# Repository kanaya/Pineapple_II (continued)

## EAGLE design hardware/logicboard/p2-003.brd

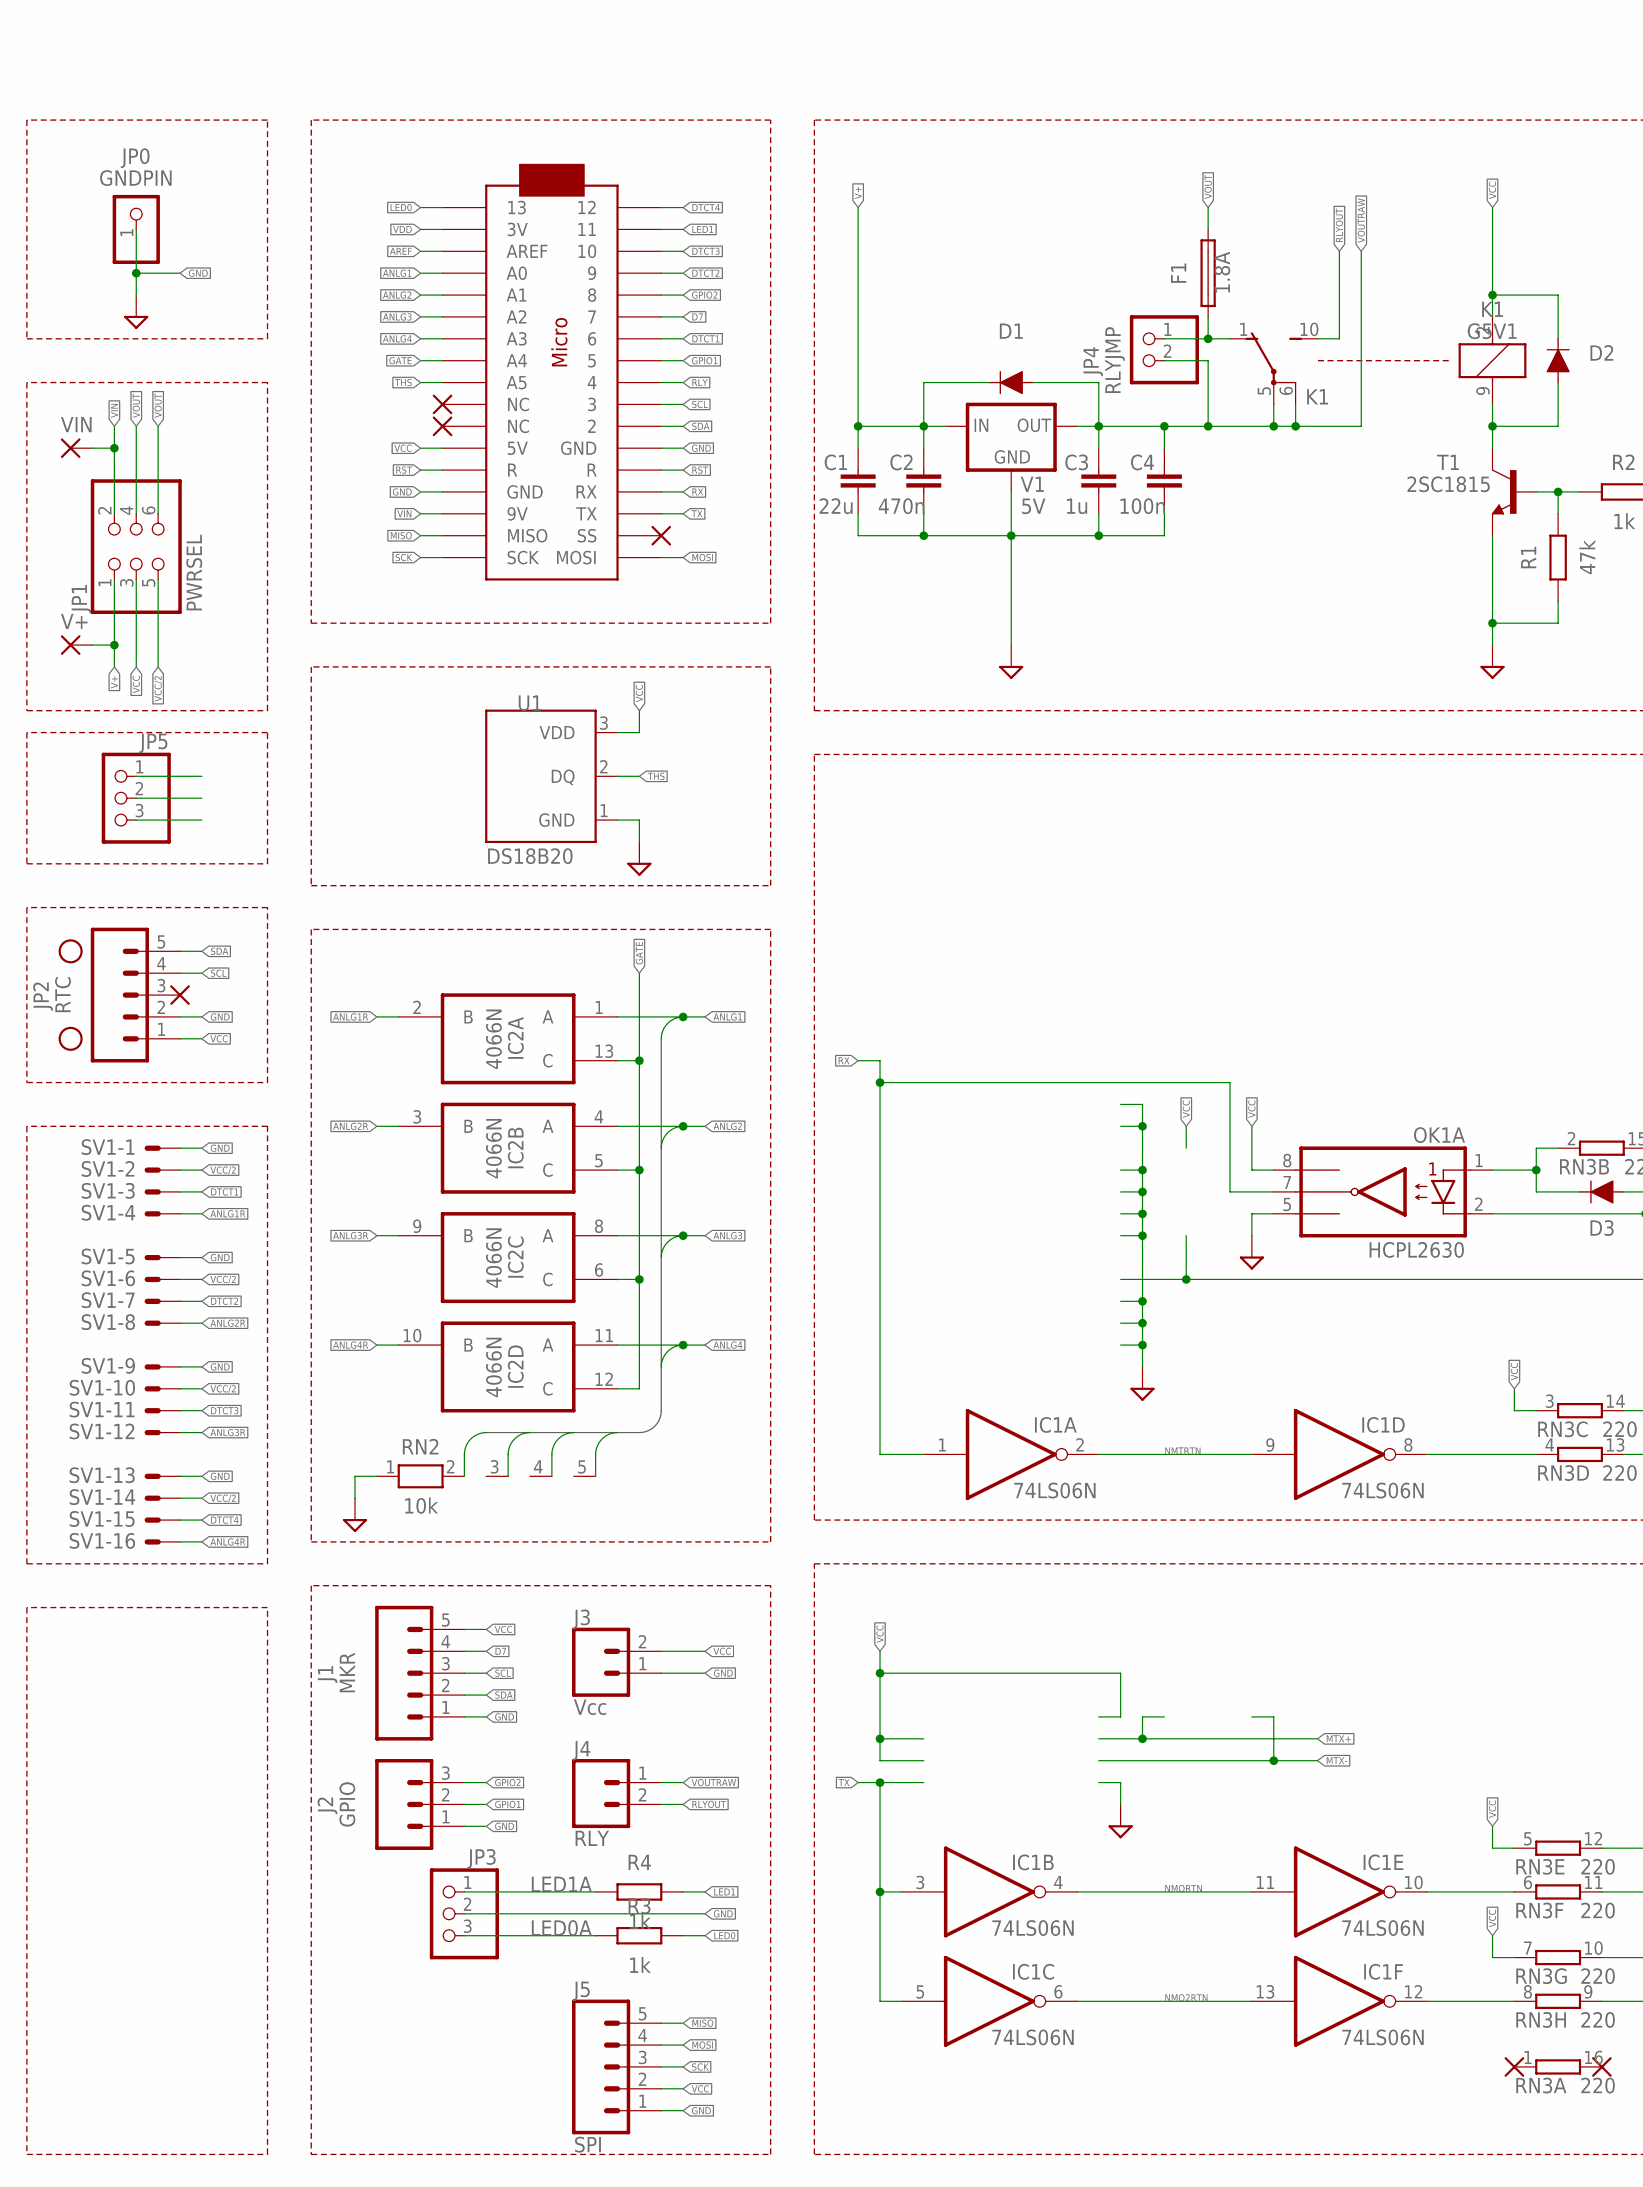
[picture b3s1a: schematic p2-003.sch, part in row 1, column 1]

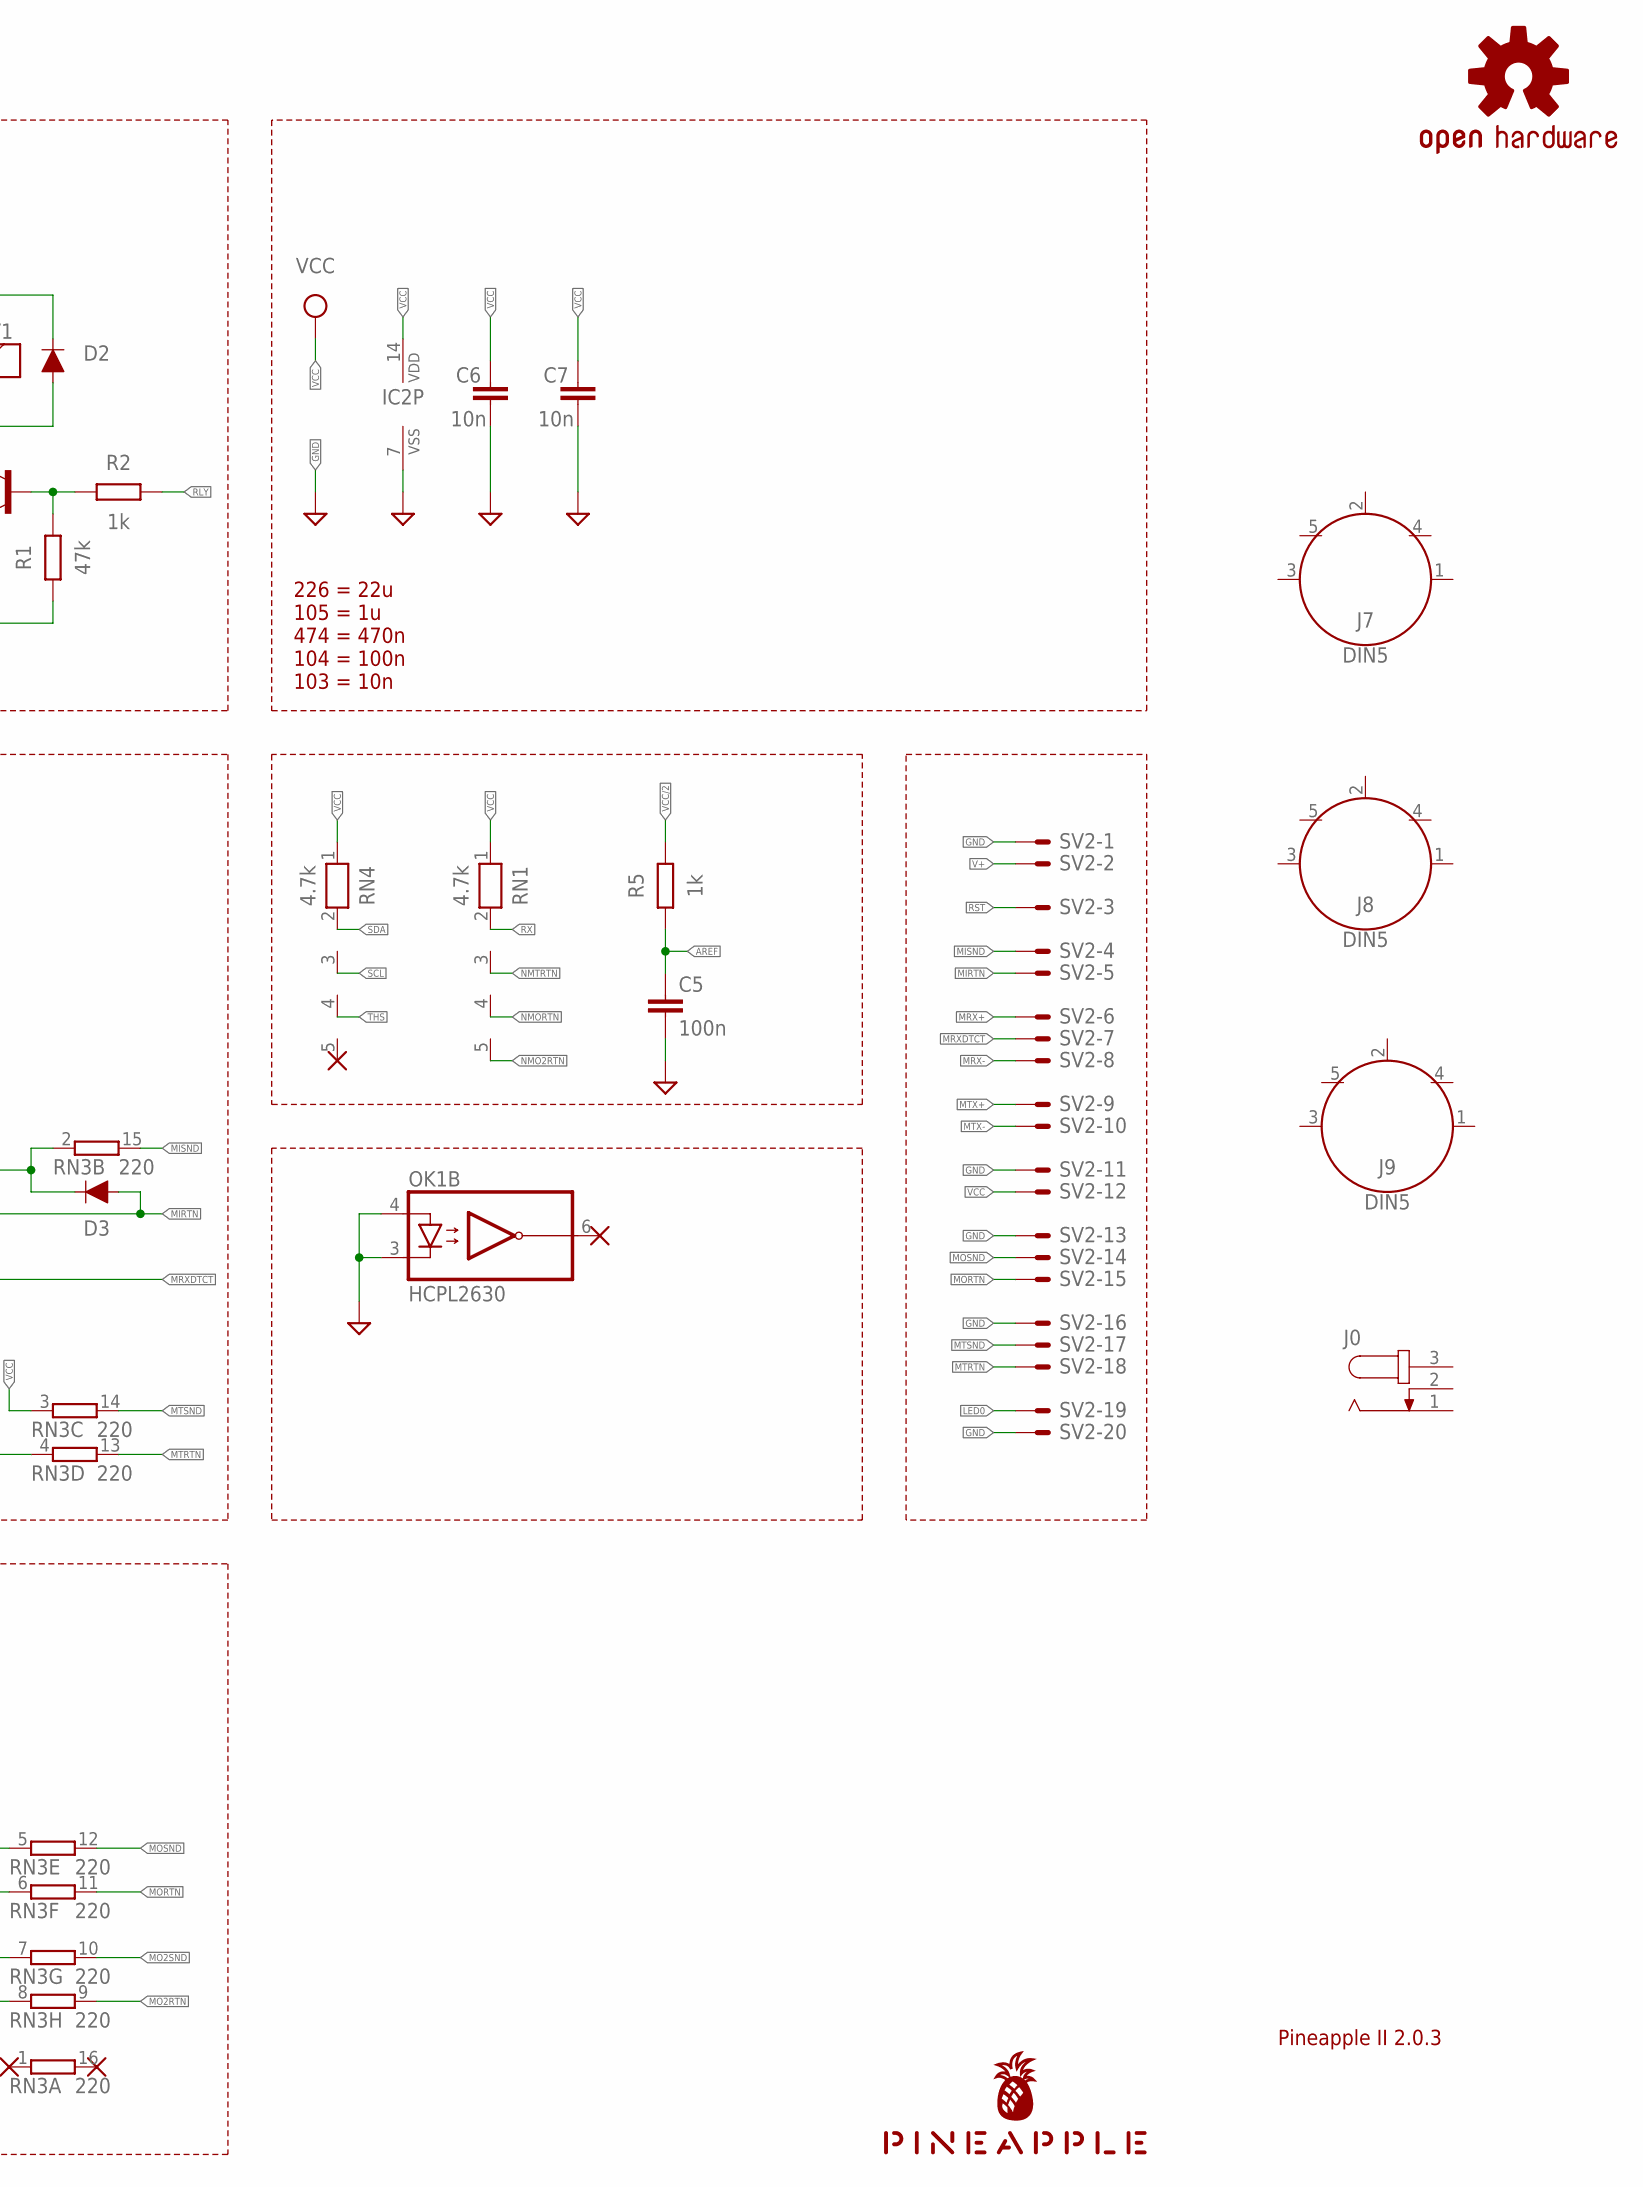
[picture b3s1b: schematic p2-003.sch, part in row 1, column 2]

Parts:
C1: 22u; C025-050X050
C2: 470n; C050-024X044
C3: 1u; C050-024X044
C4, C5: 100n; C025-024X044
C6, C7: 10n; C025-024X044
D1, D2, D3: DIODE-1N4148
F1: 1.8A; TE5
H1, H2: STAND-OFF
IC1: 74LS06N; DIL14
IC2: 4066N; DIL14
J0: JACK-PLUG0; SPC4077
J1: MKR; JST-5-PTH
J2: GPIO; JST-3-PTH
J3: Vcc; JST-2-PTH
J4: RLY; JST-2-SMD
J5: SPI; JST-5-PTH-VERT
J7, J8, J9: DIN5; DIN5-RA-PTH
JP0: GNDPIN; 1X01
JP1: PWRSEL; 2X03
JP2: RTC; 1X05
JP3, JP5: PINHD-1X3; 1X03
JP4: RLYJMP; 1X02
K1: G5V1
LOGO1: OSHW-LOGOS-COPPER; OSHW-LOGO-S_COPPER
MC1: ARDUINOMICRO
OK1: HCPL2630; DIL08
R1: 47k; 0204/5
R2, R3, R4, R5: 1k; 0204/5
RN1, RN4: 4.7k; RN-5
RN2: 10k; RN-5
RN3: 220; DIL16
SV1: ML16LE; ML16L
SV2: ML20LE; ML20L
T1: 2SC1815; TO92-ECB
U1: DS18B20; TO-92-AMMO
U$1: PINEAPPLE450_SILK
V1: 5V; 78XXL
V+: SMD2; SMD1,27-2,54
VIN: SMD2; SMD1,27-2,54

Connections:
ANLG1: IC2.1 (A), MC1.P$31 (A0), RN2.2
ANLG1R: IC2.2 (B), SV1.4
ANLG2: IC2.4 (A), MC1.P$30 (A1), RN2.3
ANLG2R: IC2.3 (B), SV1.8
ANLG3: IC2.8 (A), MC1.P$29 (A2), RN2.4
ANLG3R: IC2.9 (B), SV1.12
ANLG4: IC2.11 (A), MC1.P$28 (A3), RN2.5
ANLG4R: IC2.10 (B), SV1.16
AREF: C5.1, MC1.P$32 (AREF), R5.1
D7: J1.4, MC1.P$6 (7)
DTCT1: MC1.P$7 (6), SV1.3
DTCT2: MC1.P$4 (9), SV1.7
DTCT3: MC1.P$3 (10), SV1.11
DTCT4: MC1.P$1 (12), SV1.15
GATE: IC2.5 (C), IC2.6 (C), IC2.12 (C), IC2.13 (C), MC1.P$27 (A4)
GND: C1.2, C2.2, C3.2, C4.2, C5.2, C6.2, C7.2, IC1.7 (GND), IC2.7 (VSS), J1.1, J2.1, J3.1, J5.1, JP0.1, JP2.2, JP3.2, JP5.1, MC1.P$12 (GND), MC1.P$21 (GND), OK1.3 (C2), OK1.4 (A2), OK1.5 (GND), R1.1, RN2.1, SV1.1, SV1.5, SV1.9, SV1.13, SV2.1, SV2.11, SV2.13, SV2.16, SV2.20, T1.E, U1.1 (GND), V1.GND
GPIO1: J2.2, MC1.P$8 (5)
GPIO2: J2.3, MC1.P$5 (8)
LED0: MC1.P$34 (13), R3.2, SV2.19
LED0A: JP3.3, R3.1
LED1: MC1.P$2 (11), R4.2
LED1A: JP3.1, R4.1
MIDIINSND: D3.C, OK1.1 (A1), RN3.2 (1)
MIRTN: D3.A, OK1.2 (C1), SV2.5
MISND: RN3.15 (2), SV2.4
MISO: J5.5, MC1.P$19 (MISO)
MO2RTN: RN3.9 (2)
MO2RTNRAW: IC1.12 (O), RN3.8 (1)
MO2SND: RN3.10 (2)
MORTN: RN3.11 (2), SV2.15
MORTNRAW: IC1.10 (O), RN3.6 (1)
MOSI: J5.4, MC1.P$17 (MOSI)
MOSND: RN3.12 (2), SV2.14
MRX+: SV2.6
MRX-: SV2.8
MRXDTCT: SV2.7
MTRTN: RN3.13 (2), SV2.18
MTRTNRAW: IC1.8 (O), RN3.4 (1)
MTSND: RN3.14 (2), SV2.17
MTX+: SV2.9
MTX-: SV2.10
NMO2RTN: IC1.6 (O), IC1.13 (I), RN1.5
NMORTN: IC1.4 (O), IC1.11 (I), RN1.4
NMTRTN: IC1.2 (O), IC1.9 (I), RN1.3
RLY: MC1.P$9 (4), R2.2
RLYDRV: R1.2, R2.1, T1.B
RLYOUT: J4.2 (1), K1.10 (S)
RLYSNK: D2.A, K1.9 (2), T1.C
RST: MC1.P$13 (R), MC1.P$22 (R), SV2.3
RX: IC1.1 (I), MC1.P$14 (RX), OK1.7 (VO1), RN1.2
SCK: J5.3, MC1.P$18 (SCK)
SCL: J1.3, JP2.4, MC1.P$10 (3), RN4.3
SDA: J1.2, JP2.5, MC1.P$11 (2), RN4.2
THS: MC1.P$26 (A5), RN4.4, U1.2 (DQ)
TX: IC1.3 (I), IC1.5 (I), MC1.P$15 (TX)
V+: C1.1, C2.1, D1.C, JP1.1, JP5.3, SV2.2, V1.IN, V+.1
VCC: C6.1, C7.1, D2.C, IC1.14 (VCC), IC2.14 (VDD), J1.5, J3.2, J5.2, JP1.3, JP2.1, JP5.2, K1.2 (1), MC1.P$23 (5V), OK1.8 (VCC), RN1.1, RN3.3 (1), RN3.5 (1), RN3.7 (1), RN4.1, SV2.12, U1.3 (VDD)
VCC/2: JP1.5, R5.2, SV1.2, SV1.6, SV1.10, SV1.14
VDD: MC1.P$33 (3V)
VIN: JP1.2, MC1.P$20 (9V), VIN.1
VOUT: F1.2, JP1.4, JP1.6
VOUTRAW: C3.1, C4.1, D1.A, J4.1 (2), JP4.2, K1.5, K1.6, V1.OUT
VOUTRAW2: F1.1, JP4.1, K1.1 (O)

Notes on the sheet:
Pineapple II 2.0.3
226 = 22u 105 = 1u 474 = 470n 104 = 100n 103 = 10n

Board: 2 copper layers, 51 parts (1 on the bottom side), 55 nets, no tracks yet.

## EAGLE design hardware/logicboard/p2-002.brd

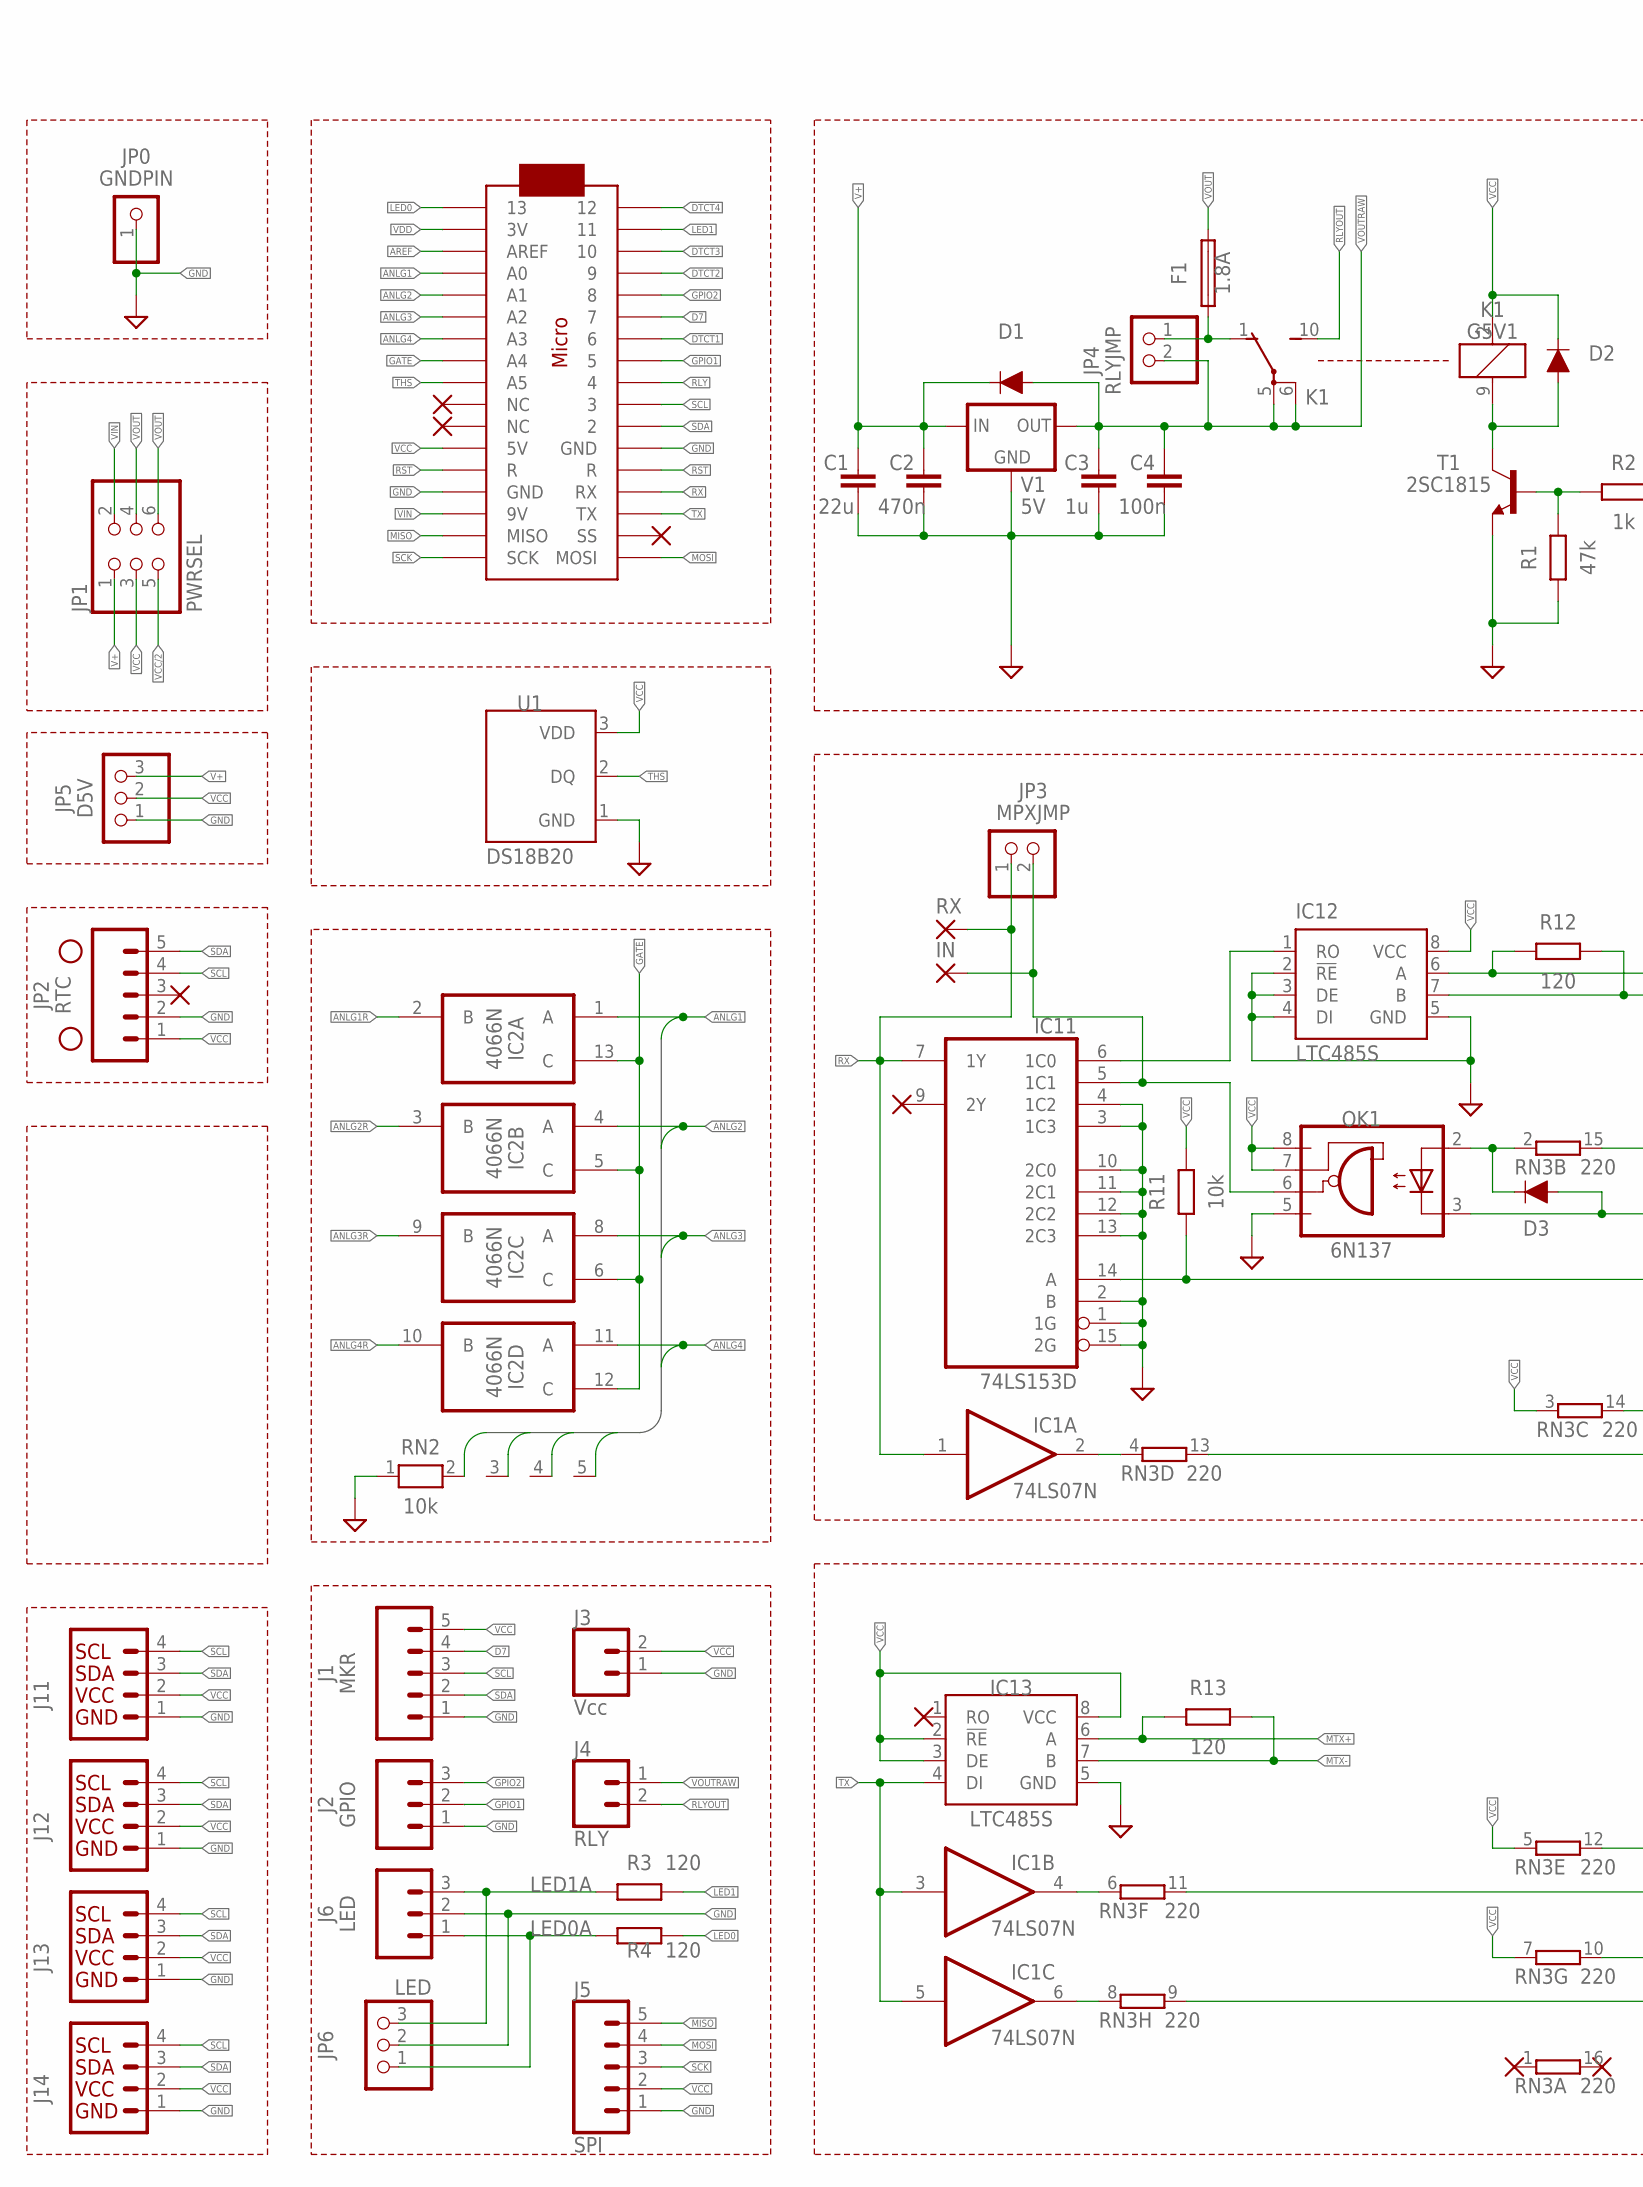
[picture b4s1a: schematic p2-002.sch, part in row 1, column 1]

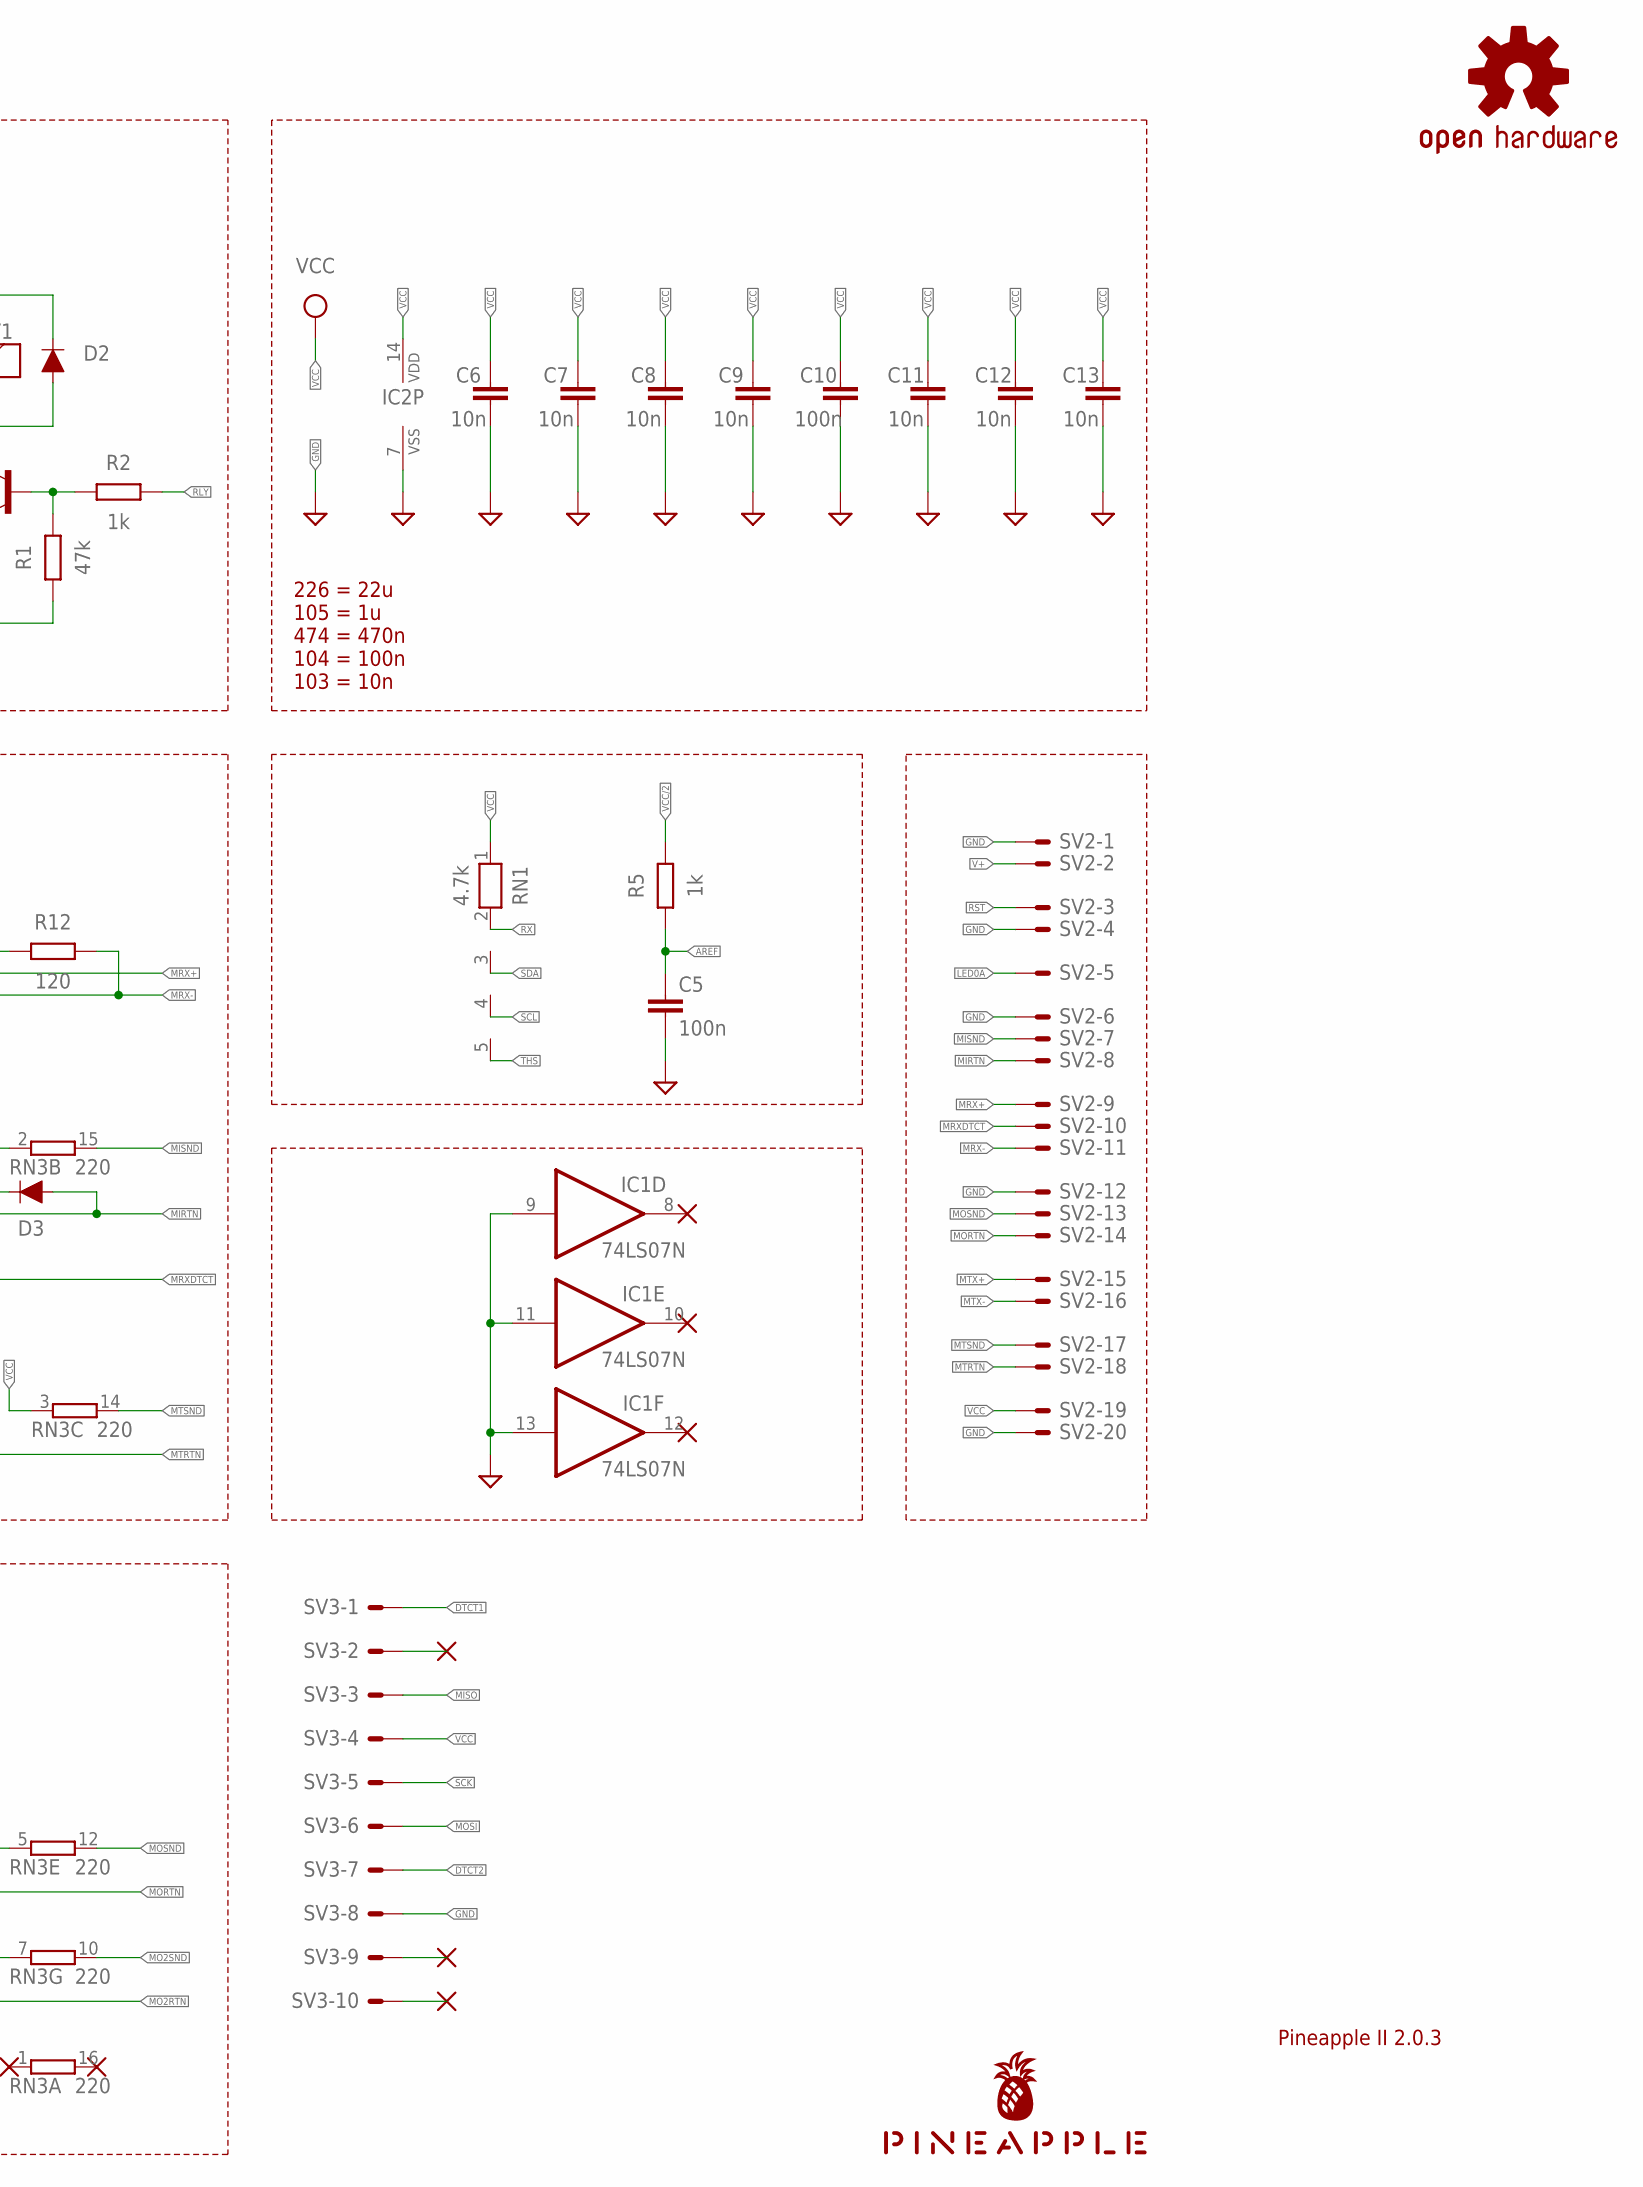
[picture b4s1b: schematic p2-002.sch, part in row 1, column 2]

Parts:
C1: 22u; C025-050X050
C2: 470n; C050-024X044
C3: 1u; C050-024X044
C4, C5, C10: 100n; C025-024X044
C6, C7, C8, C9: 10n; C025-024X044
C11, C12, C13: 10n; C2012
D1, D2, D3: DIODE-1N4148
F1: 1.8A; TE5
H1, H2: STAND-OFF
IC1: 74LS07N; DIL14
IC2: 4066N; DIL14
IC11: 74LS153D; SO16
IC12, IC13: LTC485S; SOIC8
IN: SMD2; SMD1,27-2,54
J1: MKR; JST-5-PTH
J2: GPIO; JST-3-PTH
J3: Vcc; JST-2-PTH
J4: RLY; JST-2-SMD
J5: SPI; JST-5-PTH-VERT
J6: LED; JST-3-PTH
J11, J12, J13, J14: Qwiic; 1X04_1MM_RA
JP0: GNDPIN; 1X01
JP1: PWRSEL; 2X03
JP2: RTC; 1X05
JP3: MPXJMP; 1X02
JP4: RLYJMP; 1X02
JP5: D5V; 1X03
JP6: LED; 1X03
K1: G5V1
LOGO1: OSHW-LOGOS-COPPER; OSHW-LOGO-S_COPPER
MC1: ARDUINOMICRO
OK1: 6N137; DIL08
R1: 47k; 0204/5
R2, R5: 1k; 0204/5
R3, R4: 120; 0204/5
R11: 10k; M2012
R12, R13: 120; M2012
RN1: 4.7k; RN-5
RN2: 10k; RN-5
RN3: 220; DIL16
RX: SMD2; SMD1,27-2,54
SV2: ML20LE; ML20L
SV3: ML10LE; ML10L
T1: 2SC1815; TO92-ECB
U1: DS18B20; TO-92-AMMO
U$1: PINEAPPLE450_SILK
V1: 5V; 78XXL

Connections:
ANLG1: IC2.1 (A), MC1.P$31 (A0), RN2.2
ANLG1R: IC2.2 (B)
ANLG2: IC2.4 (A), MC1.P$30 (A1), RN2.3
ANLG2R: IC2.3 (B)
ANLG3: IC2.8 (A), MC1.P$29 (A2), RN2.4
ANLG3R: IC2.9 (B)
ANLG4: IC2.11 (A), MC1.P$28 (A3), RN2.5
ANLG4R: IC2.10 (B)
AREF: C5.1, MC1.P$32 (AREF), R5.1
D7: J1.4, MC1.P$6 (7)
DTCT1: MC1.P$7 (6), SV3.1
DTCT2: MC1.P$4 (9), SV3.7
DTCT3: MC1.P$3 (10)
DTCT4: MC1.P$1 (12)
GATE: IC2.5 (C), IC2.6 (C), IC2.12 (C), IC2.13 (C), MC1.P$27 (A4)
GND: C1.2, C2.2, C3.2, C4.2, C5.2, C6.2, C7.2, C8.2, C9.2, C10.2, C11.2, C12.2, C13.2, IC1.7 (GND), IC1.9 (I), IC1.11 (I), IC1.13 (I), IC2.7 (VSS), IC11.1 (1G), IC11.2 (B), IC11.3 (1C3), IC11.4 (1C2), IC11.8 (GND), IC11.10 (2C0), IC11.11 (2C1), IC11.12 (2C2), IC11.13 (2C3), IC11.15 (2G), IC12.2 (!RE), IC12.3 (DE), IC12.4 (DI), IC12.5 (GND), IC13.5 (GND), J1.1, J2.1, J3.1, J5.1, J6.2, J11.1 (GND), J12.1 (GND), J13.1 (GND), J14.1 (GND), JP0.1, JP2.2, JP5.1, JP6.2, MC1.P$12 (GND), MC1.P$21 (GND), OK1.5 (GND), R1.1, RN2.1, SV2.1, SV2.4, SV2.6, SV2.12, SV2.20, SV3.8, T1.E, U1.1 (GND), V1.GND
GPIO1: J2.2, MC1.P$8 (5)
GPIO2: J2.3, MC1.P$5 (8)
LED0: MC1.P$34 (13), R4.2
LED0A: J6.1, JP6.1, R4.1, SV2.5
LED1: MC1.P$2 (11), R3.2
LED1A: J6.3, JP6.3, R3.1
MIDIINSND: D3.C, OK1.2 (A), RN3.2 (1)
MIN: IC11.5 (1C1), IN.1, JP3.2, OK1.6 (VO)
MIRTN: D3.A, OK1.3 (C), SV2.8
MISND: RN3.15 (2), SV2.7
MISO: J5.5, MC1.P$19 (MISO), SV3.3
MO: IC1.4 (O), RN3.6 (1)
MO2: IC1.6 (O), RN3.8 (1)
MO2RTN: RN3.9 (2)
MO2SND: RN3.10 (2)
MORTN: RN3.11 (2), SV2.14
MOSI: J5.4, MC1.P$17 (MOSI), SV3.6
MOSND: RN3.12 (2), SV2.13
MRX: IC11.6 (1C0), IC12.1 (RO)
MRX+: IC12.6 (A), R12.1, SV2.9
MRX-: IC12.7 (B), R12.2, SV2.11
MRXDTCT: IC11.14 (A), R11.1, SV2.10
MT: IC1.2 (O), RN3.4 (1)
MTRTN: RN3.13 (2), SV2.18
MTSND: RN3.14 (2), SV2.17
MTX+: IC13.6 (A), R13.1, SV2.15
MTX-: IC13.7 (B), R13.2, SV2.16
NC1: SV3.2
NC2: SV3.9
NC3: SV3.10
RLY: MC1.P$9 (4), R2.2
RLYDRV: R1.2, R2.1, T1.B
RLYOUT: J4.2 (1), K1.10 (S)
RLYSNK: D2.A, K1.9 (2), T1.C
RST: MC1.P$13 (R), MC1.P$22 (R), SV2.3
RX: IC1.1 (I), IC11.7 (1Y), JP3.1, MC1.P$14 (RX), RN1.2, RX.1
SCK: J5.3, MC1.P$18 (SCK), SV3.5
SCL: J1.3, J11.4 (SCL), J12.4 (SCL), J13.4 (SCL), J14.4 (SCL), JP2.4, MC1.P$10 (3), RN1.4
SDA: J1.2, J11.3 (SDA), J12.3 (SDA), J13.3 (SDA), J14.3 (SDA), JP2.5, MC1.P$11 (2), RN1.3
THS: MC1.P$26 (A5), RN1.5, U1.2 (DQ)
TX: IC1.3 (I), IC1.5 (I), IC13.4 (DI), MC1.P$15 (TX)
V+: C1.1, C2.1, D1.C, JP1.1, JP5.3, SV2.2, V1.IN
VCC: C6.1, C7.1, C8.1, C9.1, C10.1, C11.1, C12.1, C13.1, D2.C, IC1.14 (VCC), IC2.14 (VDD), IC11.16 (VCC), IC12.8 (VCC), IC13.2 (!RE), IC13.3 (DE), IC13.8 (VCC), J1.5, J3.2, J5.2, J11.2 (VCC), J12.2 (VCC), J13.2 (VCC), J14.2 (VCC), JP1.3, JP2.1, JP5.2, K1.2 (1), MC1.P$23 (5V), OK1.7 (VE), OK1.8 (VCC), R11.2, RN1.1, RN3.3 (1), RN3.5 (1), RN3.7 (1), SV2.19, SV3.4, U1.3 (VDD)
VCC/2: JP1.5, R5.2
VDD: MC1.P$33 (3V)
VIN: JP1.2, MC1.P$20 (9V)
VOUT: F1.2, JP1.4, JP1.6
VOUTRAW: C3.1, C4.1, D1.A, J4.1 (2), JP4.2, K1.5, K1.6, V1.OUT
VOUTRAW2: F1.1, JP4.1, K1.1 (O)

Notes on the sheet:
Pineapple II 2.0.3
226 = 22u 105 = 1u 474 = 470n 104 = 100n 103 = 10n

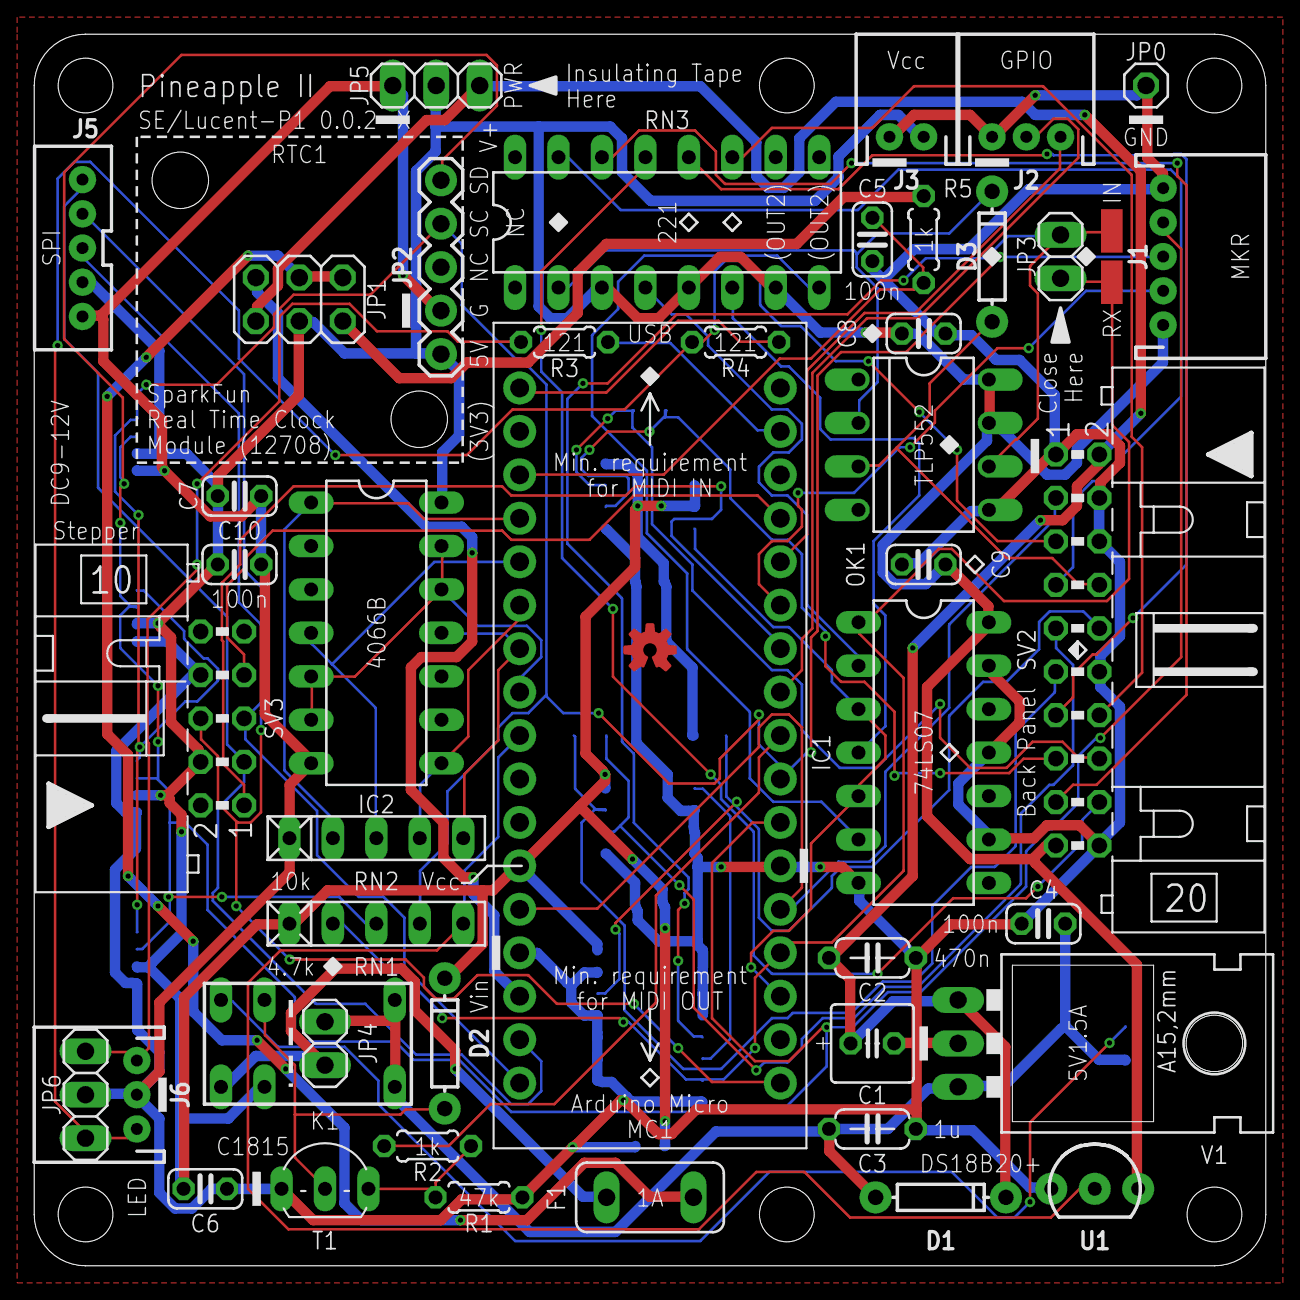
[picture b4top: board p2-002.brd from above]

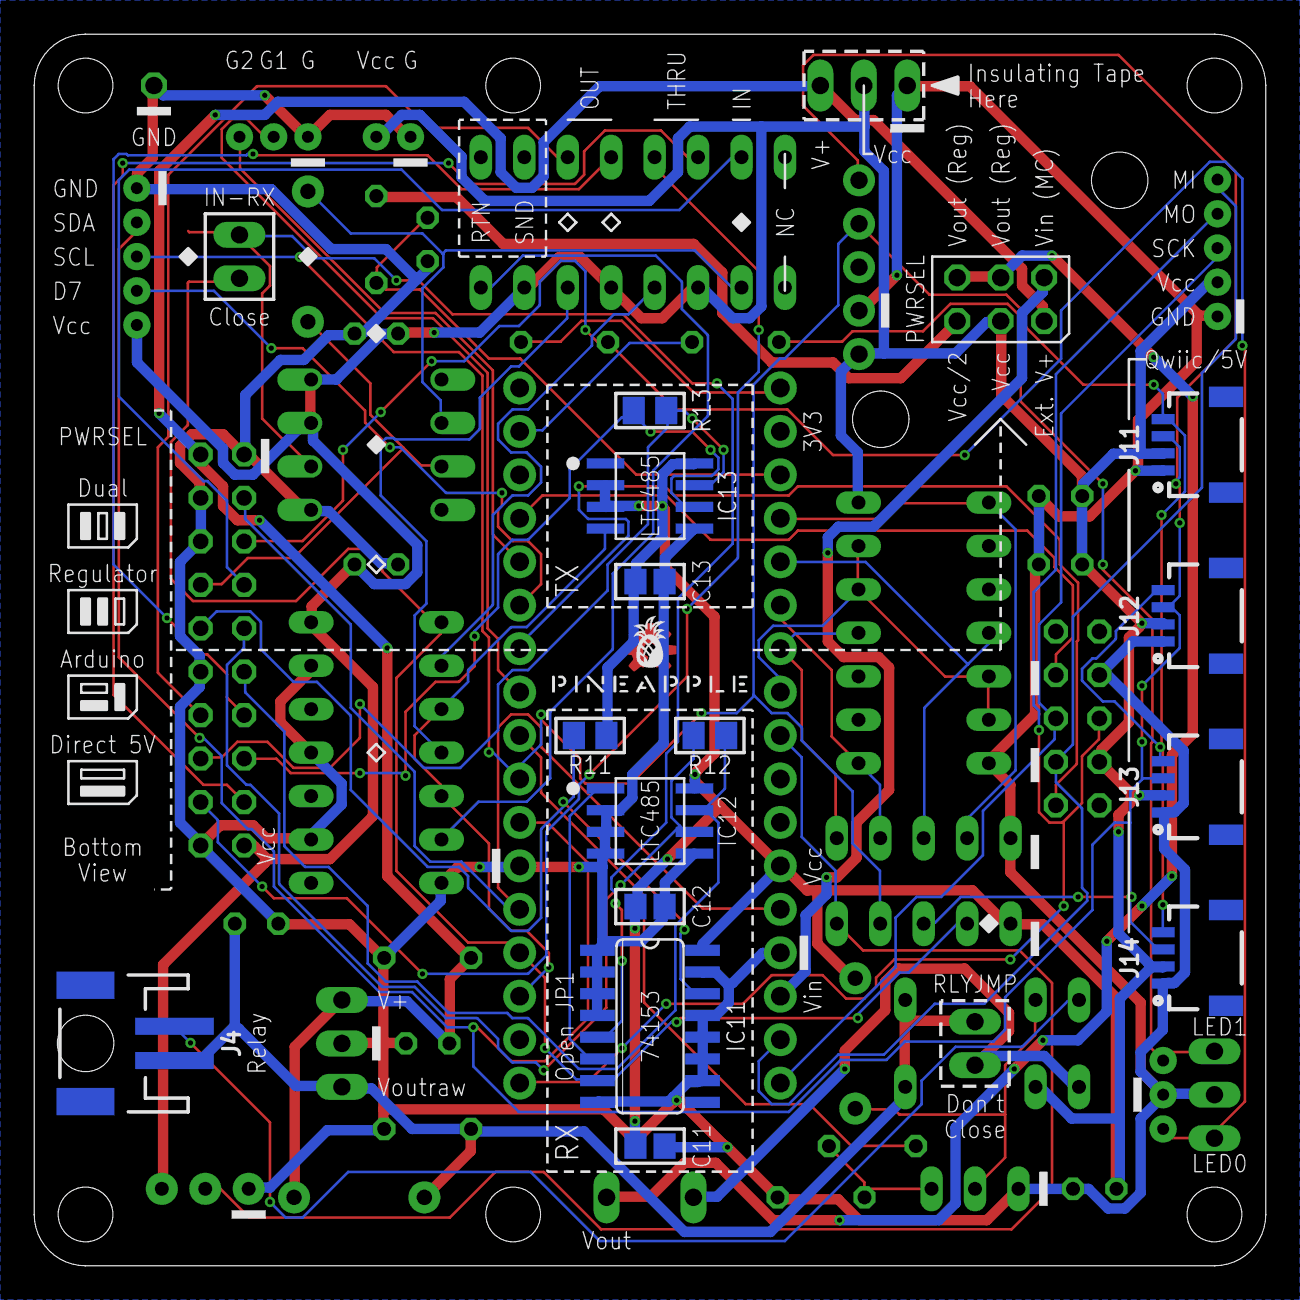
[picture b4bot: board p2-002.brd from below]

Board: 2 copper layers, 72.0 x 72.0 mm, 64 parts (15 on the bottom side), 53 nets.
